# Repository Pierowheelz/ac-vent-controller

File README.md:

# Ducted Air Conditioner Vent Controller
This project uses an ESP32-based controller, stepper motors, TMC2209 (or similar) drivers and endstop switches (from a 3d printer kit) to control the circular Air Conditioner vents used in many ducted HVAC systems.
Each board can control up to 4 vents (leave the stepper header empty and tweak the /AC_Vent/config.h to control fewer vents). Multiple boards can be utilised to control more vents, or for vents too far from one board.

# Home Automation
This project is part of a larger ecosystem, designed to enable automation of vents based on the room temperatures, along with an App for manual control.
* [home-app-backend](https://github.com/Pierowheelz/home-app-backend) - backend API and automation logic
* [home-control](https://github.com/Pierowheelz/home-control) - web app for manual control

## Parts Required
* ESP32 Dev Board (NodeMCU-ESP32 DEVKITV1 - 30 pins - based on ESP-WROOM-32)
* 3D Printer Kit (from ebay or Aliexpress)
    * 4x Nema 17 stepper motors + cables
    * 4x Nema 17 mounting brackets
    * 4x Stepper motors drivers - A4988 or DRV8825 or TMC2208 (for quieter operation)
    * 4x RAMPS 1.4 switch endstops + cables (Note, swap the trigger switch for a waterproof one for more reliable operation, but keep the switch PCB)
* Order the PCB from the Gerber files (or custom-build with Perfboard 24 x 18 pins)
* 4x 150mm Lead screws + copper nuts (4mm pitch ideal, but any will work)
* DC-DC Buck convertor TRS2433 (or you can use an LM2596 set to 3.3v if DIYing the board)
* DC power supply (8-35 V)
* (optional) header-pin sockets for ESP32 and Stepper Drivers to allow quick removal/replacement
* A handfull of M4 screws & nuts
* Duct tape

## Process
1. Order the custom PCM from the Gerber files in the Circuit Board V2/ directory.
1. Print 4x Motor Bracket, Motor Cover, Endstop Clip in PLA or PETG (or other hard-plastic).
1. Print 4x Coupler, Damper and 8x End Holder in TPU (for vibration damping - PLA will work in a pinch though). Metal couplers from a 3d printer kit can also be used.
1. Assemble the circuitboard per the KiCad schematic or using the silk screen guides.
1. Set the ventNames, microStepping, WiFi parameters in the firmware (see AC_Vent/README_CONFIG.md for details).
1. Compile and flash the firmware onto your ESP32 dev board using Arduino IDE.
    * Using USB for power (do not plug in the power supply for this).
    * NOTE: Setup Arduino IDE with ESP32 library like this: https://randomnerdtutorials.com/installing-the-esp32-board-in-arduino-ide-windows-instructions/
1. Bench test by connecting motors and endstop switches.
    * You may need to switch the red and black wires on your endstop switches (black should be at the edge of the board, and red in the middle).
1. Connect the power supply to the high-voltage side of the buck convertor. This will power up the ESP32.
1. Tune the stepper motor current limit (Try this guide: https://www.makerguides.com/a4988-stepper-motor-driver-arduino-tutorial/).
    * Using USB for power (do not plug in the power supply for this).
1. On a computer, navigate to the IP Address of the device.
1. Click to open one of the Vents.
    * It will first spin counter-clockwise to close the vent until the endstop switch is triggered, then clockwise until the limit position is reached.
	* Note: If the motor spins the wrong direction, simply unplug and reverse it's connector.
1. Assemble components and install into vents. Tip: use Ethernet cable to extend leads as neccessary (I used RJ45 breakout modules but you could crimp connectors).

Note: There is no security or authentication in this system. Do not open up the port in your Router! For use on your internal network only.

## Usage via Rest API
Get vents status: `GET http://192.168.2.110/?&t=1`

Sample return:
```
{
	"0": {
		"name": "Room #1",
		"pos": 30
	},
	"1": {
		"name": "Room #2",
		"pos": 60
	},
	"2": {
		"name": "Room #3",
		"pos": 100
	}
}
```

Open vent `#1` to 100%: `GET http://192.168.2.110/?a=6&t=1&m=0&d=100`
Here `a` is the operating mode, where mode 6 corresponds to: open to ratio set by &d= (eg. ?d=050:open50%, ?d=000:close, ?d=100:open100%).
Also, `t` is the response type (1 = JSON).
And, `m` is the motor number (0-2).

The return format is identical to the 'get status' request.

## Images
Note: Some photos are from the prototype.

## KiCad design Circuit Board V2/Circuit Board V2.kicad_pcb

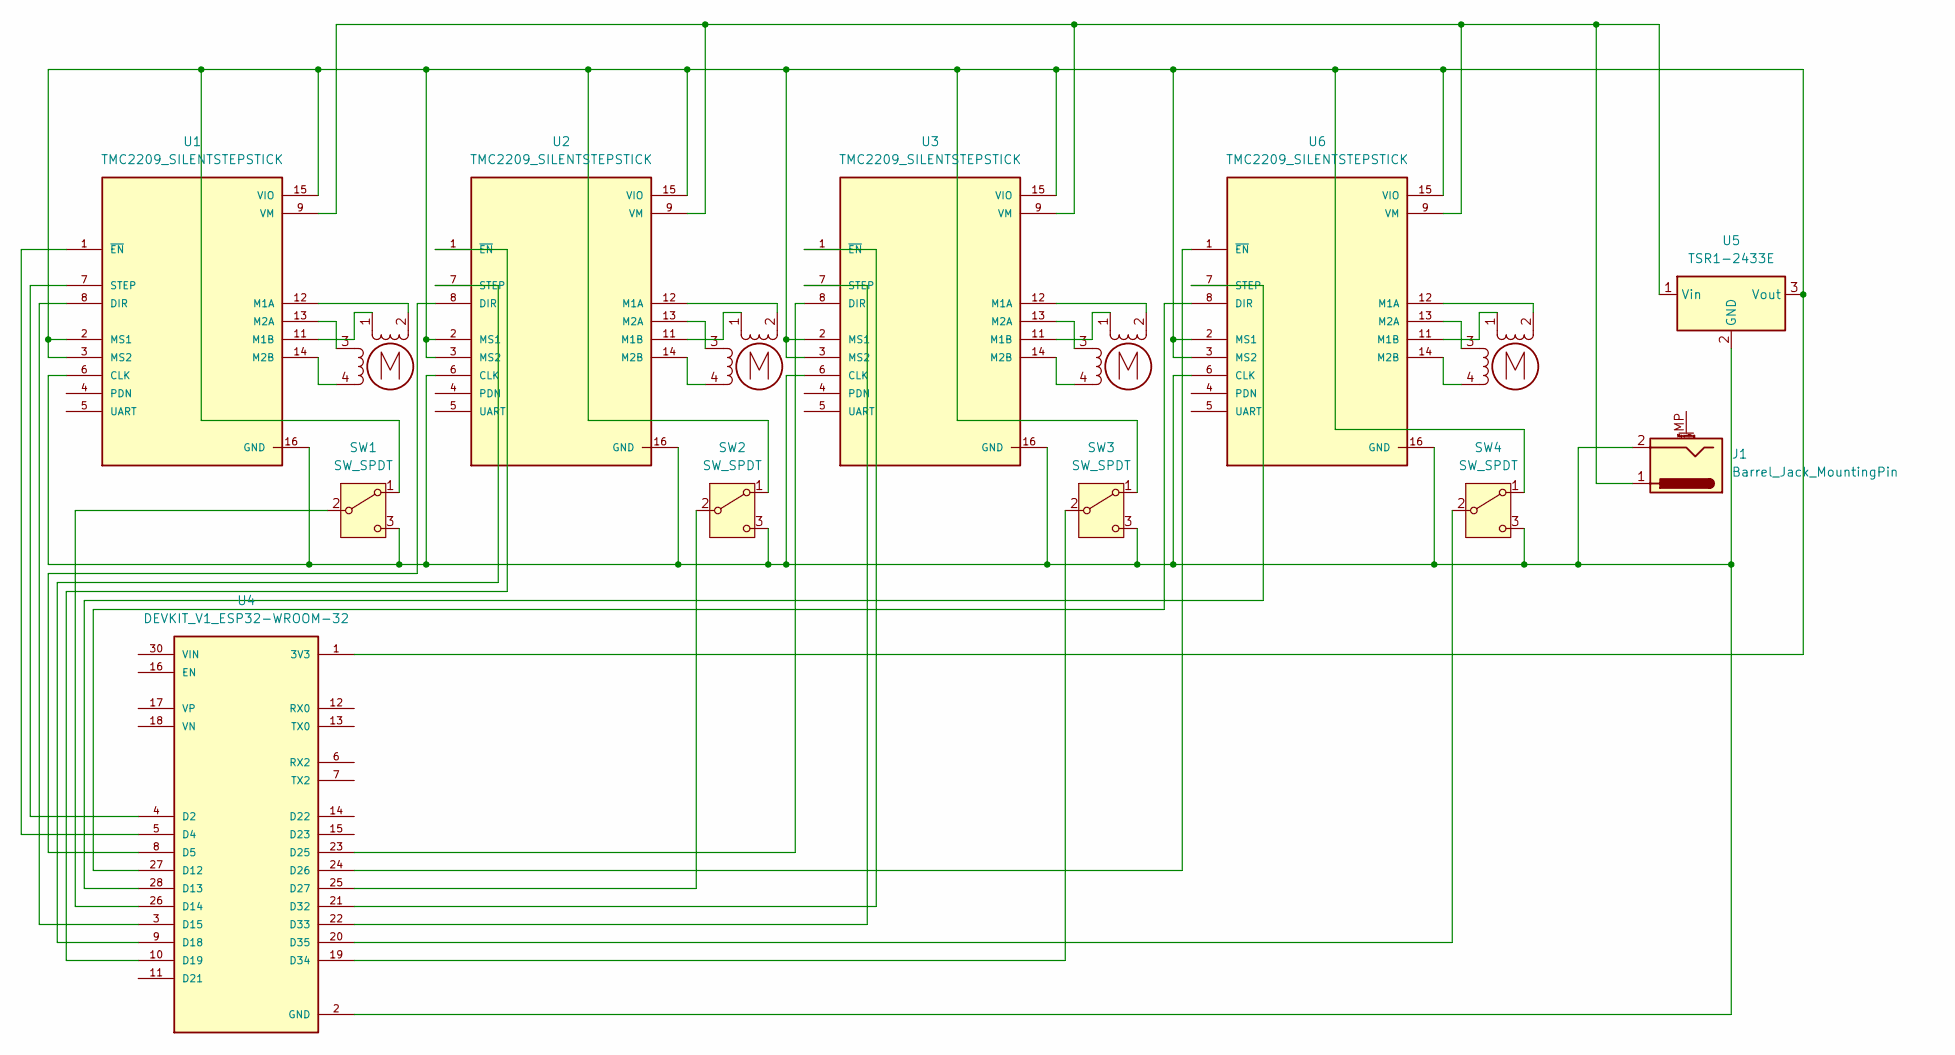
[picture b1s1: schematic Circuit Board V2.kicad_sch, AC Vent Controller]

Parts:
J1: Barrel_Jack_MountingPin; BarrelJack_Horizontal
M1, M2, M3, M4: Stepper_Motor_bipolar; PinHeader_1x04_P2.54mm_Vertical
SW1, SW2, SW3, SW4: SW_SPDT; SW_Slide-03_Wuerth-WS-SLTV_10x2.5x6.4_P2.54mm
U1, U2, U3, U6: TMC2209_SILENTSTEPSTICK; MODULE_TMC2209_SILENTSTEPSTICK; PARTREV 1.20
U4: DEVKIT_V1_ESP32-WROOM-32; MODULE_DEVKIT_V1_ESP32-WROOM-32
U5: TSR1-2433E; Converter_DCDC_TRACO_TSR1-xxxxE_THT

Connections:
GND: J1.2, SW1.3 (C), SW2.3 (C), SW3.3 (C), SW4.3 (C), U1.6 (CLK), U1.10 (GND), U1.16 (GND), U2.6 (CLK), U2.10 (GND), U2.16 (GND), U3.6 (CLK), U3.10 (GND), U3.16 (GND), U4.2 (GND), U4.29 (GND), U5.2 (GND), U6.6 (CLK), U6.10 (GND), U6.16 (GND)
unnamed: M1.2 (-_2), U1.12 (M1A)
unnamed: M2.2 (-_2), U2.12 (M1A)
unnamed: M3.2 (-_2), U3.12 (M1A)
unnamed: M4.2 (-_2), U6.12 (M1A)
unnamed: SW1.1 (A), SW2.1 (A), SW3.1 (A), SW4.1 (A), U1.2 (MS1), U1.3 (MS2), U1.15 (VIO), U2.2 (MS1), U2.3 (MS2), U2.15 (VIO), U3.2 (MS1), U3.3 (MS2), U3.15 (VIO), U4.1 (3V3), U5.3 (Vout), U6.2 (MS1), U6.3 (MS2), U6.15 (VIO)
unnamed: SW1.2 (B), U4.26 (D14)
unnamed: SW2.2 (B), U4.25 (D27)
unnamed: SW3.2 (B), U4.19 (D34)
unnamed: SW4.2 (B), U4.20 (D35)
unnamed: U1.8 (DIR), U4.3 (D15)
unnamed: M1.1, U1.11 (M1B)
unnamed: M1.3, U1.13 (M2A)
unnamed: M1.4, U1.14 (M2B)
unnamed: U1.7 (STEP), U4.4 (D2)
unnamed: J1.1, U1.9 (VM), U2.9 (VM), U3.9 (VM), U5.1 (Vin), U6.9 (VM)
unnamed: U1.1 (~EN), U4.5 (D4)
unnamed: U2.8 (DIR), U4.8 (D5)
unnamed: M2.1, U2.11 (M1B)
unnamed: M2.3, U2.13 (M2A)
unnamed: M2.4, U2.14 (M2B)
unnamed: U2.7 (STEP), U4.9 (D18)
unnamed: U2.1 (~EN), U4.10 (D19)
unnamed: U3.8 (DIR), U4.23 (D25)
unnamed: M3.1, U3.11 (M1B)
unnamed: M3.3, U3.13 (M2A)
unnamed: M3.4, U3.14 (M2B)
unnamed: U3.7 (STEP), U4.22 (D33)
unnamed: U3.1 (~EN), U4.21 (D32)
unnamed: U4.27 (D12), U6.8 (DIR)
unnamed: U4.28 (D13), U6.7 (STEP)
unnamed: U4.24 (D26), U6.1 (~EN)
unnamed: M4.1, U6.11 (M1B)
unnamed: M4.3, U6.13 (M2A)
unnamed: M4.4, U6.14 (M2B)

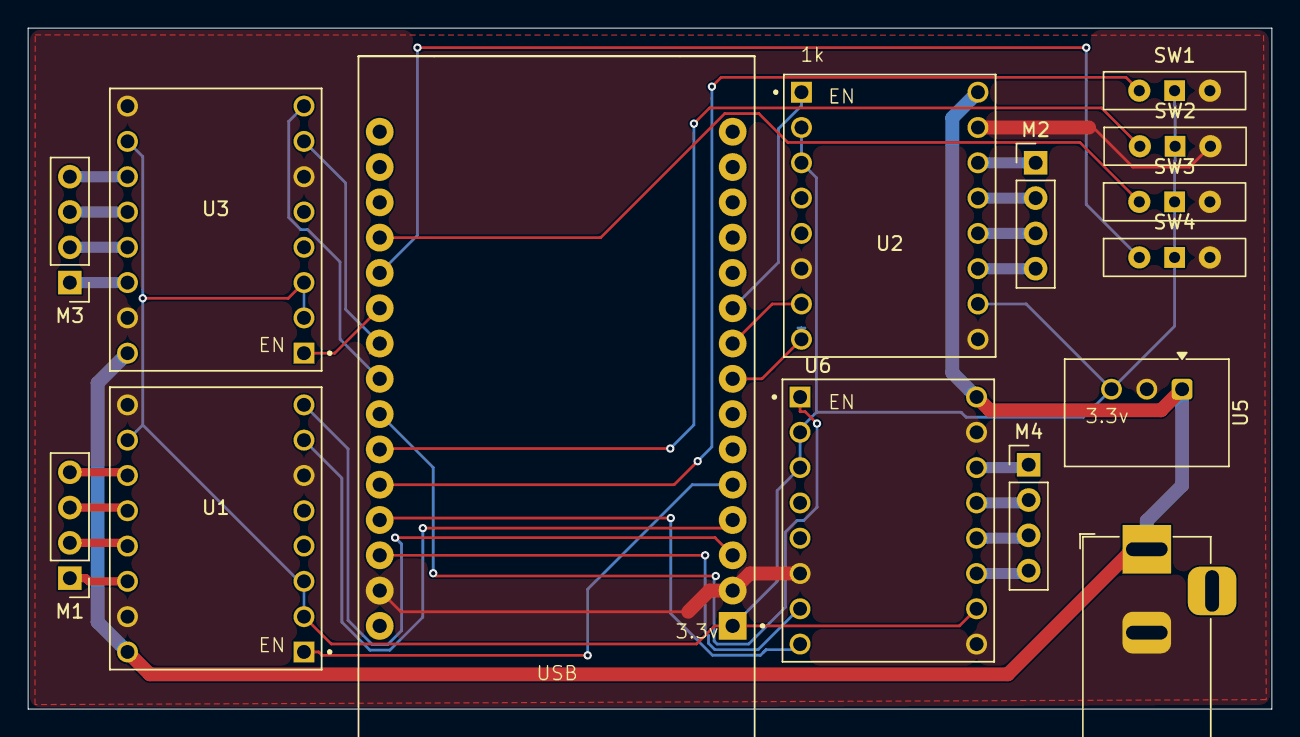
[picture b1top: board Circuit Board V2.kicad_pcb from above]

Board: 2 copper layers, 89.5 x 49.0 mm, 15 parts (0 on the bottom side), 35 nets.

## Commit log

2020-08-22 Initial git commit
    Added additional resources. Begun work on adding microstepping (incomplete). Non-functional build.
2020-08-22 Completed setup of Microstepping. Reassinged pins per Circuit Baord
2020-08-22 Changed GPIO pins due to bootloop. Updated documentation
2020-08-22 Added pictures
2020-08-22 Steppers off on startup. Updated readme.
2020-08-22 Updated board schematic
2020-08-23 Added Fusion360/Eagle Schematic. Updated readme.
2020-09-27 Fixed WiFi connection to work with hidden SSIDs. Generalised connection details.
2020-09-27 Fixed setup() error.
2021-12-28 Added simple JSON API
2025-05-29 Removed EEPROM state saving in favour of simply checking endstop status on init
2026-01-27 Created seperate config file + Fixed crashes, WiFi disconnects and timeouts.
2026-04-13 Rafactor including plenty of bugfixes.
2026-04-18 Rewrite for TMC2209 steppers with sensorless homing (no endstops).
2026-04-18 Fixes for homing short distances (or zero distance).
2026-04-18 Added v2 circuit board design (no endstops)
2026-05-16 v 1.7.0
2026-05-31 Added PCB schematic of current version (v2)
